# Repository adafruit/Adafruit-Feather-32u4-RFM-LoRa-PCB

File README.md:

## Adafruit Feather 32u4 RFM LoRa Radios PCB

<br/>
Click below to purchase one from the Adafruit shop

PCB files for the Adafruit Feather 32u4 RFM69 and LoRa Radio. Format is EagleCAD schematic and board layout

For more details, check out the product pages at
* RFM69HCW Packet Radio - 868 or 915 MHz https://www.adafruit.com/product/3076
* RFM69HCW Packet Radio - 433MHz https://www.adafruit.com/product/3077
* RFM95 LoRa Radio- 868 or 915 MHz https://www.adafruit.com/product/3078
* RFM96 LoRa Radio - 433MHz https://www.adafruit.com/product/3079

### Description

We call these RadioFruits, our take on an microcontroller packet radio transceiver with built in USB and battery charging. Its an Adafruit Feather 32u4 with a radio module cooked in! Great for making wireless networks that can go further than 2.4GHz 802.15.4 and similar, are more flexible than Bluetooth LE and without the high power requirements of WiFi.

Feather is the new development board from Adafruit, and like its namesake it is thin, light, and lets you fly! We designed Feather to be a new standard for portable microcontroller cores.

### License

Adafruit invests time and resources providing this open source design, please support Adafruit and open-source hardware by purchasing products from [Adafruit](https://www.adafruit.com)!

Designed by Limor Fried/Ladyada for Adafruit Industries.

Creative Commons Attribution/Share-Alike, all text above must be included in any redistribution. See license.txt for additional details.

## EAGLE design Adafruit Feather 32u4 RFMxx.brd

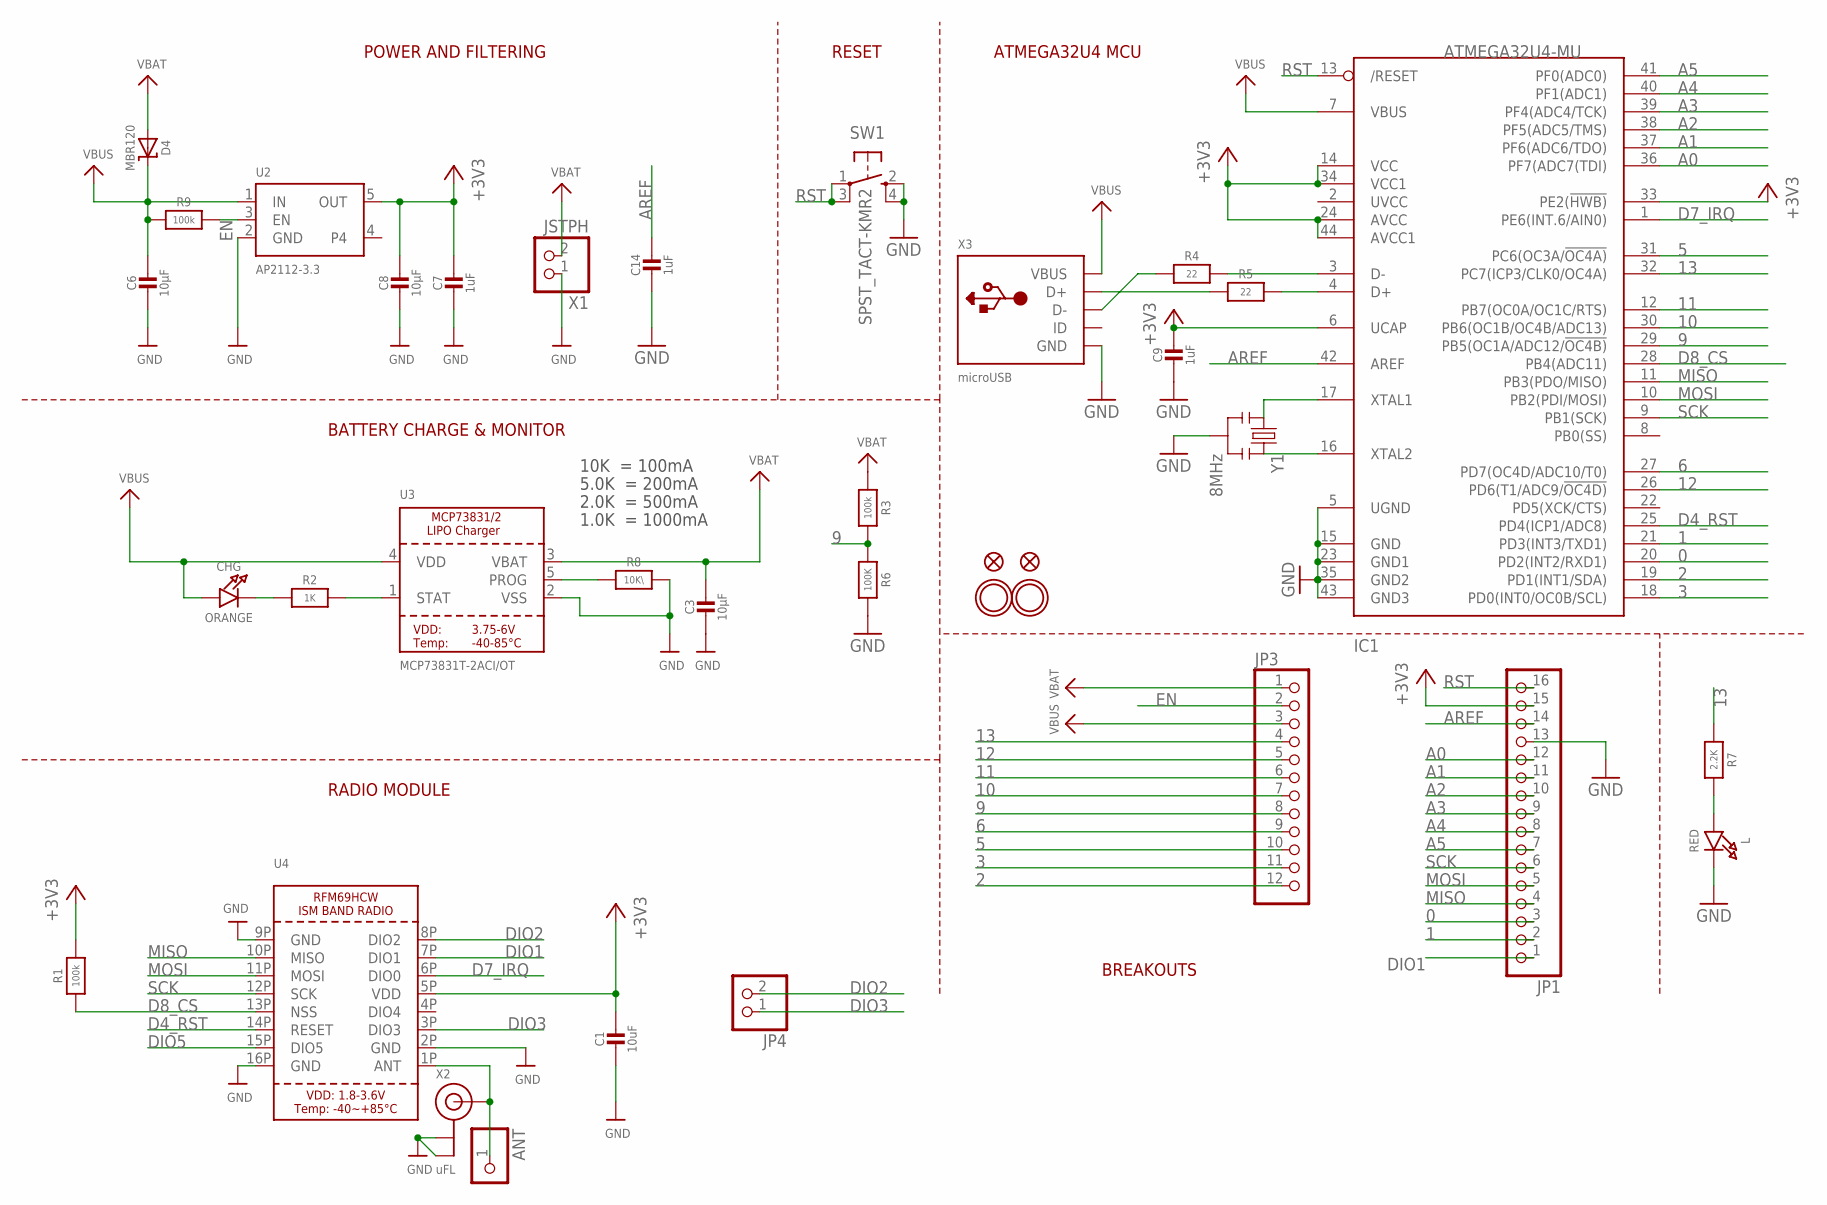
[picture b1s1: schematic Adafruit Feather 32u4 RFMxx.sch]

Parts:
ANT: HEADER-1X1ROUND; 1X01_ROUND
C1: 10uF; 0805-NO
C3, C6, C8: 10µF; 0805-NO
C7, C14: 1uF; 0603-NO
C9: 1uF; _0603MP
CHG: ORANGE; CHIPLED_0805_NOOUTLINE
D4: MBR120; SOD-123
IC1: ATMEGA32U4-MU; TQFN44_7MM
JP1: HEADER-1X16ROUND; 1X16_ROUND
JP3: HEADER-1X12; 1X12_ROUND
JP4: HEADER-1X2ROUND; 1X02_ROUND
L: RED; CHIPLED_0805_NOOUTLINE
R1, R3, R9: 100k; 0603-NO
R2: 1K; 0603-NO
R4, R5: 22; 0603-NO
R6: 100K; 0603-NO
R7: 2.2K; 0603-NO
R8: 10K\; 0603-NO
SW1: SPST_TACT-KMR2; KMR2
U2: AP2112-3.3; SOT23-5
U3: MCP73831T-2ACI/OT; SOT23-5
U4: RFM69HCW_SMT; RFMHCW_SMT
U$31, U$32: MOUNTINGHOLE2.5; MOUNTINGHOLE_2.5_PLATED
U$34, U$35: FIDUCIAL""; FIDUCIAL_1MM
X1: JSTPH; JSTPH2
X2: uFL; U.FL
X3: microUSB; 4UCONN_20329_V2
Y1: 8MHz; RESONATOR-SMD

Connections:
0: IC1.20 (PD2(INT2/RXD1)), JP1.3
1: IC1.21 (PD3(INT3/TXD1)), JP1.2
2: IC1.19 (PD1(INT1/SDA)), JP3.12
3: IC1.18 (PD0(INT0/OC0B/SCL)), JP3.11
5: IC1.31 (PC6(OC3A/!OC4A)), JP3.10
6: IC1.27 (PD7(OC4D/ADC10/T0)), JP3.9
9: IC1.29 (PB5(OC1A/ADC12/!OC4B)), JP3.8, R3.2, R6.1
10: IC1.30 (PB6(OC1B/OC4B/ADC13)), JP3.7
11: IC1.12 (PB7(OC0A/OC1C/RTS)), JP3.6
12: IC1.26 (PD6(T1/ADC9/!OC4D)), JP3.5
13: IC1.32 (PC7(ICP3/CLK0/OC4A)), JP3.4, R7.1
+3V3: C1.1, C7.1, C8.1, C9.1, IC1.6 (UCAP), IC1.14 (VCC), IC1.24 (AVCC), IC1.33 (PE2(!HWB)), IC1.34 (VCC1), IC1.44 (AVCC1), JP1.15, R1.2, U2.5 (OUT), U4.5P (VDD)
A0: IC1.36 (PF7(ADC7(TDI)), JP1.12
A1: IC1.37 (PF6(ADC6/TDO)), JP1.11
A2: IC1.38 (PF5(ADC5/TMS)), JP1.10
A3: IC1.39 (PF4(ADC4/TCK)), JP1.9
A4: IC1.40 (PF1(ADC1)), JP1.8
A5: IC1.41 (PF0(ADC0)), JP1.7
ANT: ANT.1, U4.1P (ANT), X2.3 (SIGNAL)
AREF: C14.1, IC1.42 (AREF), JP1.14
D4_RST: IC1.25 (PD4(ICP1/ADC8)), U4.14P (RESET)
D7_IRQ: IC1.1 (PE6(INT.6/AIN0)), U4.6P (DIO0)
D8_CS: IC1.28 (PB4(ADC11)), R1.1, U4.13P (NSS)
D+: IC1.4 (D+), R5.2
D-: IC1.3 (D-), R4.2
DIO1: JP1.1, U4.7P (DIO1)
DIO2: JP4.2, U4.8P (DIO2)
DIO3: JP4.1, U4.3P (DIO3)
DIO5: U4.15P (DIO5)
EN: JP3.2, R9.2, U2.3 (EN)
GND: C1.2, C3.2, C6.2, C7.2, C8.2, C9.2, C14.2, IC1.5 (UGND), IC1.15 (GND), IC1.23 (GND1), IC1.35 (GND2), IC1.43 (GND3), JP1.13, L.C, R6.2, R8.2, SW1.2 (S), SW1.4 (S1), U2.2 (GND), U3.2 (VSS), U4.2P (GND), U4.9P (GND), U4.16P (GND), X1.1, X2.1 (GND), X2.2 (GND), X3.BASE@1 (GND), X3.BASE@2 (GND), X3.GND, X3.SPRT@1 (GND), X3.SPRT@2 (GND), X3.SPRT@3 (GND), X3.SPRT@4 (GND), Y1.2
MISO: IC1.11 (PB3(PDO/MISO)), JP1.4, U4.10P (MISO)
MOSI: IC1.10 (PB2(PDI/MOSI)), JP1.5, U4.11P (MOSI)
unnamed: CHG.C, R2.1
unnamed: L.A, R7.2
unnamed: R2.2, U3.1 (STAT)
unnamed: R8.1, U3.5 (PROG)
unnamed: IC1.16 (XTAL2), Y1.3
unnamed: IC1.17 (XTAL1), Y1.1
unnamed: R5.1, X3.D+
unnamed: R4.1, X3.D-
RST: IC1.13 (/RESET), JP1.16, SW1.1, SW1.3 (P1)
SCK: IC1.9 (PB1(SCK)), JP1.6, U4.12P (SCK)
VBAT: C3.1, D4.A, JP3.1, R3.1, U3.3 (VBAT), X1.2
VBUS: C6.1, CHG.A, D4.C, IC1.7 (VBUS), JP3.3, R9.1, U2.1 (IN), U3.4 (VDD), X3.VBUS

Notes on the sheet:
POWER AND FILTERING
RESET
ATMEGA32U4 MCU
10K = 100mA
5.0K = 200mA
2.0K = 500mA
1.0K = 1000mA
BATTERY CHARGE & MONITOR
BREAKOUTS
RADIO MODULE

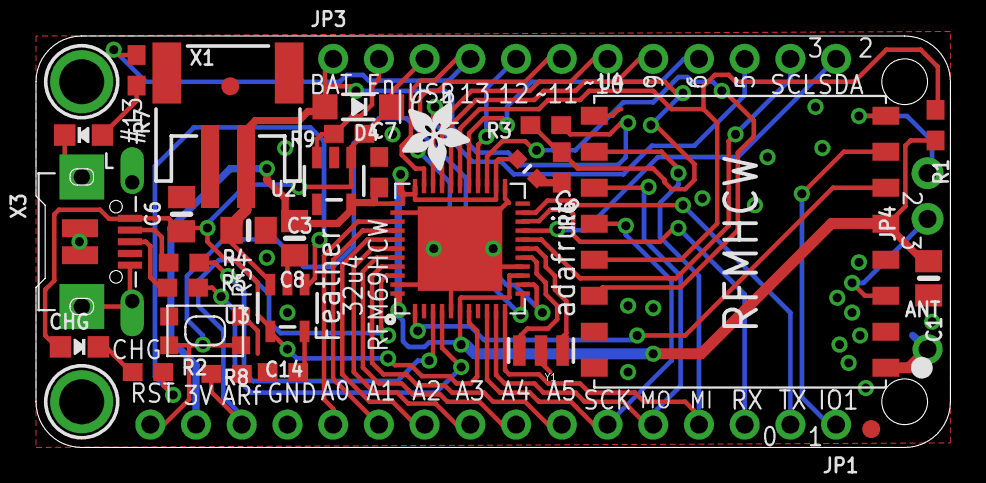
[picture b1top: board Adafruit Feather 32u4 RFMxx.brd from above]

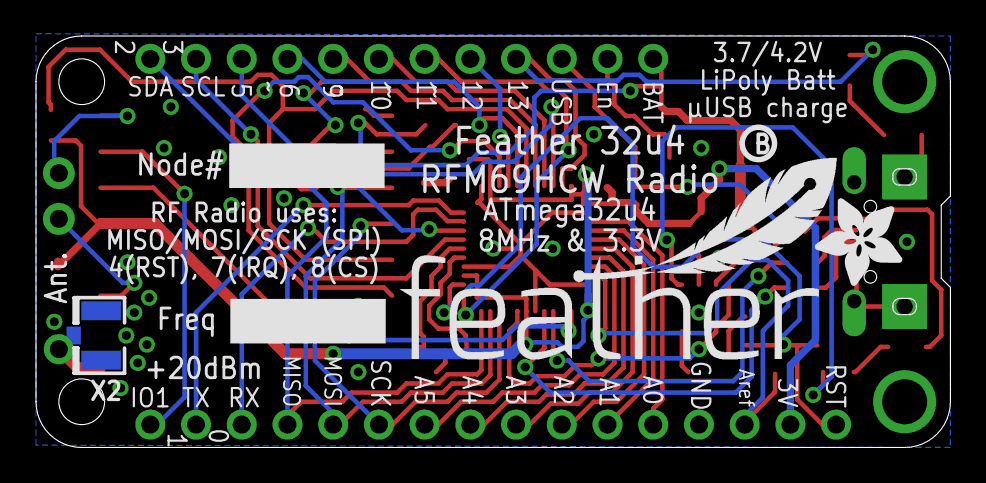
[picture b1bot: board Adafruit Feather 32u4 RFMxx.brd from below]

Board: 2 copper layers, 50.8 x 22.9 mm, 40 parts (4 on the bottom side), 44 nets.

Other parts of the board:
U$4: ADAFRUIT_5MM
U$5: FEATHERLOGO
U$6: PCBFEAT-REV-040
U$7: ADAFRUIT_3.5MM

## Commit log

2016-06-08 init
2016-12-09 fix one routed but still DRC'ing trace
2017-01-19 fix broken #8 trace
2022-04-13 Added PrettyPins

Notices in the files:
parts and their libraries:
microbuilder: This work is placed in the public domain, and may be freely used for commercial and non-commercial work with the following conditions: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
SparkFun: Licensing: CC v3.0 Share-Alike You are welcome to use this library for commercial purposes.
